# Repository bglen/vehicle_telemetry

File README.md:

# Vehicle Telemetry System

*Note: This is a work in progress and many features are not implemented yet.*

The Vehicle Telemetry System is an offline-first, containerized CAN data logging system. The system is designed to provide live telemetry and data logging for race cars, but can easilly be adapted to any mobile vehicle or robotic platform that uses CAN networks.

# Architecture Overview

### Current Features
- Logs CAN and decodes to CSV file
- Ability to decode using multiple DBC files
- Access and download decoded log files on the logger's local WiFi hotspot
- Handles sudden power loss gracefully
- Supports two CAN 2.0B networks up to 1 Mbps
- Logs data from NMEA format USB GPS devices

### Future Functionality
- Stores data to local influxDB database when logging offline. Syncs data to cloud database when internet access is detected.
- Bluetooth control of action cameras (GoPro, DJI Action)

# Data Logger

## Hardware Overview

This repo contains the hardware design for an open-source Raspberry Pi-based CAN data logger.

- Raspberry Pi 4 Model B
- 12V nominal power
- Can log two CAN networks
- GPIO for remote button for log start/stop and logging status LEDs
- Real time clock for accurate data time-stamps when not connected to internet
- Temperature, pressure, and humidity SPI sensor
- Bus voltage logging

## Datalogger Software Setup

1. Create a fresh install of Raspberry Pi OS on your Pi 4B
2. Connect to your Pi via SSH or other methods. Ensure it has an internet connection.
3. Update apt and install git and jq: `sudo apt upgrade -y && sudo apt install -y git jq`
4. Clone the repo: `git clone https://github.com/bglen/vehicle_telemetry`
5. Go to the setup folder: `cd vehicle_telemetry/software/datalogger/setup`
6. Make **install.sh** executable: `chmod +x install.sh`
7. Run the installer: `./install.sh`
8. During the install, enter in your preferred access point network name and trusted network details.
9. Reboot the Pi: `sudo reboot`

# Data Visualiation Tool

A python data visualization tool is provided and uses **rerun.io** to visualize .CSV log files.

## License
MIT License

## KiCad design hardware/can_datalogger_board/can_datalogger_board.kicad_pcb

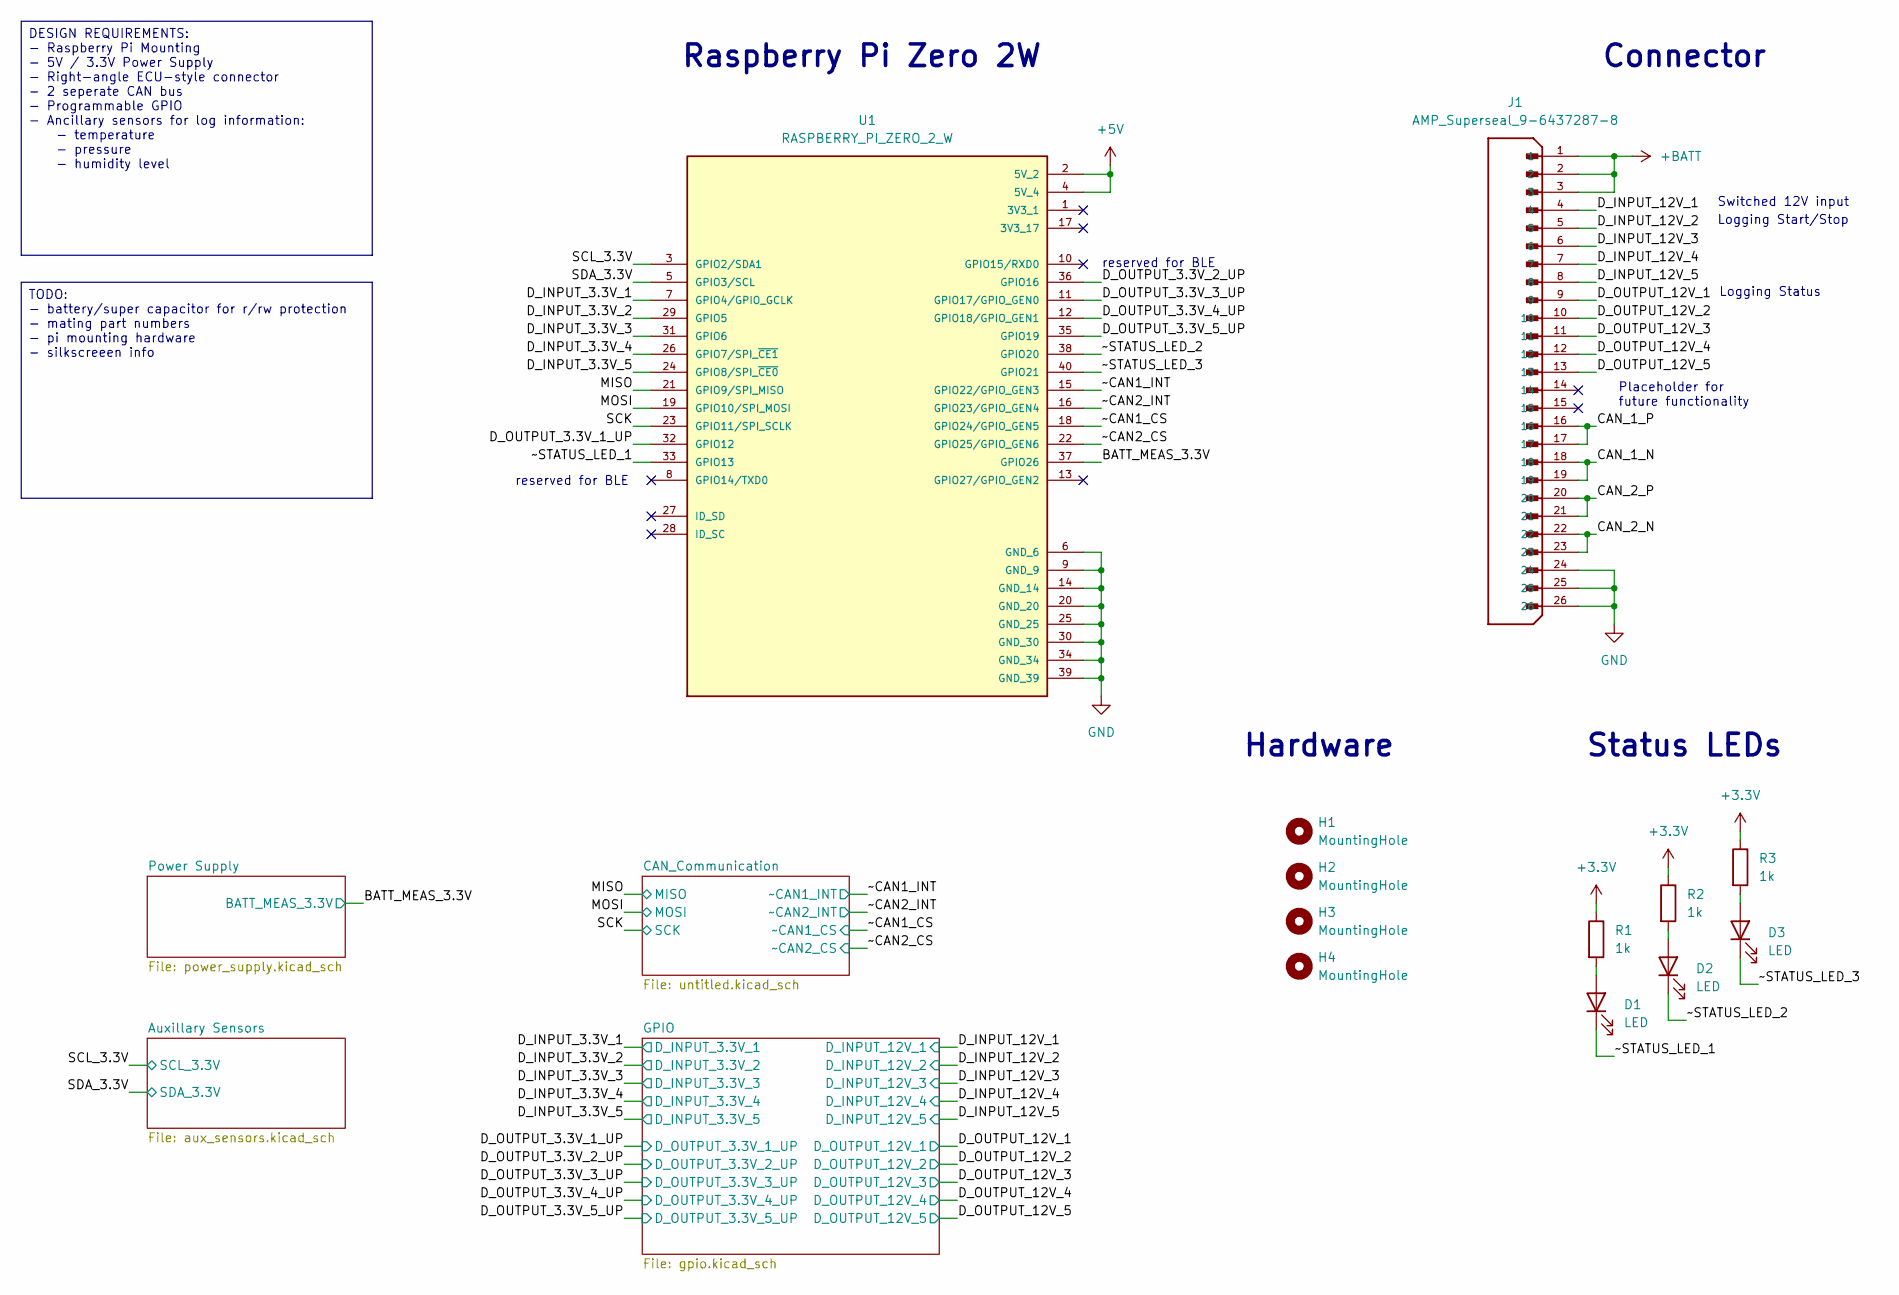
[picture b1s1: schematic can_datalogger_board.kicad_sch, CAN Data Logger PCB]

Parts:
D1, D2, D3: LED; LED_0603_1608Metric
H1, H2, H3, H4: MountingHole; MountingHole_3.2mm_M3
J1: AMP_Superseal_9-6437287-8; TE_9-6437287-8; PARTREV A1
R1, R2, R3: 1k; R_0603_1608Metric
U1: RASPBERRY_PI_ZERO_2_W; MODULE_RASPBERRY_PI_ZERO_2_W; PARTREV April 2024

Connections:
+3.3V: R1.1, R2.1, R3.1; also elsewhere on the board
+5V: U1.2 (5V_2), U1.4 (5V_4); also elsewhere on the board
+BATT: J1.1, J1.2, J1.3; also elsewhere on the board
/BATT_MEAS_3.3V: U1.37 (GPIO26)
/CAN_1_N: J1.18, J1.19
/CAN_1_P: J1.16, J1.17
/CAN_2_N: J1.22, J1.23
/CAN_2_P: J1.20, J1.21
/D_INPUT_3.3V_1: U1.7 (GPIO4/GPIO_GCLK); also elsewhere on the board
/D_INPUT_3.3V_2: U1.29 (GPIO5); also elsewhere on the board
/D_INPUT_3.3V_3: U1.31 (GPIO6); also elsewhere on the board
/D_INPUT_3.3V_4: U1.26 (GPIO7/SPI_~CE1); also elsewhere on the board
/D_INPUT_3.3V_5: U1.24 (GPIO8/SPI_~CE0); also elsewhere on the board
/D_INPUT_12V_1: J1.4; also elsewhere on the board
/D_INPUT_12V_2: J1.5; also elsewhere on the board
/D_INPUT_12V_3: J1.6; also elsewhere on the board
/D_INPUT_12V_4: J1.7; also elsewhere on the board
/D_INPUT_12V_5: J1.8; also elsewhere on the board
/D_OUTPUT_3.3V_1_UP: U1.32 (GPIO12); also elsewhere on the board
/D_OUTPUT_3.3V_2_UP: U1.36 (GPIO16); also elsewhere on the board
/D_OUTPUT_3.3V_3_UP: U1.11 (GPIO17/GPIO_GEN0); also elsewhere on the board
/D_OUTPUT_3.3V_4_UP: U1.12 (GPIO18/GPIO_GEN1); also elsewhere on the board
/D_OUTPUT_3.3V_5_UP: U1.35 (GPIO19); also elsewhere on the board
/D_OUTPUT_12V_1: J1.9; also elsewhere on the board
/D_OUTPUT_12V_2: J1.10; also elsewhere on the board
/D_OUTPUT_12V_3: J1.11; also elsewhere on the board
/D_OUTPUT_12V_4: J1.12; also elsewhere on the board
/D_OUTPUT_12V_5: J1.13; also elsewhere on the board
/MISO: U1.21 (GPIO9/SPI_MISO); also elsewhere on the board
/MOSI: U1.19 (GPIO10/SPI_MOSI); also elsewhere on the board
/SCK: U1.23 (GPIO11/SPI_SCLK); also elsewhere on the board
/SCL_3.3V: U1.3 (GPIO2/SDA1); also elsewhere on the board
/SDA_3.3V: U1.5 (GPIO3/SCL); also elsewhere on the board
/~CAN1_CS: U1.18 (GPIO24/GPIO_GEN5); also elsewhere on the board
/~CAN1_INT: U1.15 (GPIO22/GPIO_GEN3); also elsewhere on the board
/~CAN2_CS: U1.22 (GPIO25/GPIO_GEN6); also elsewhere on the board
/~CAN2_INT: U1.16 (GPIO23/GPIO_GEN4); also elsewhere on the board
/~STATUS_LED_1: D1.1 (K), U1.33 (GPIO13)
/~STATUS_LED_2: D2.1 (K), U1.38 (GPIO20)
/~STATUS_LED_3: D3.1 (K), U1.40 (GPIO21)
GND: J1.24, J1.25, J1.26, U1.6 (GND_6), U1.9 (GND_9), U1.14 (GND_14), U1.20 (GND_20), U1.25 (GND_25), U1.30 (GND_30), U1.34 (GND_34), U1.39 (GND_39); also elsewhere on the board
unnamed: D1.2 (A), R1.2
unnamed: D2.2 (A), R2.2
unnamed: D3.2 (A), R3.2

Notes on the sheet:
Switched 12V input
reserved for BLE
Status LEDs
Logging Start/Stop
Logging Status
Connector
Hardware
Raspberry Pi Zero 2W
Placeholder for future functionality
TODO: - battery/super capacitor for r/rw protection - mating part numbers - pi mounting hardware - silkscreeen info
DESIGN REQUIREMENTS: - Raspberry Pi Mounting - 5V / 3.3V Power Supply - Right-angle ECU-style connector - 2 seperate CAN bus - Programmable GPIO - Ancillary sensors for log information: - temperature - pressure - humidity level

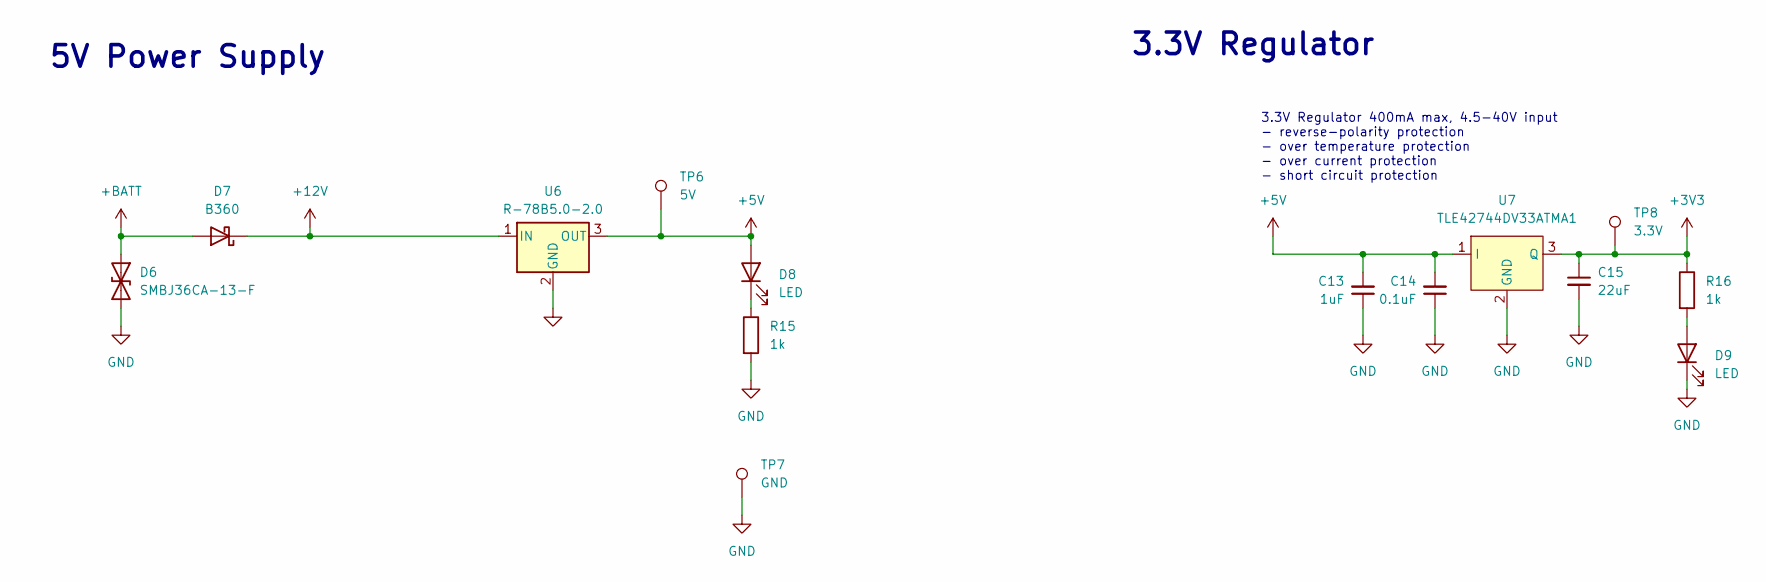
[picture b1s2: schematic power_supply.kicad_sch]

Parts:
C13: 1uF; C_0603_1608Metric
C14: 0.1uF; C_0603_1608Metric
C15: 22uF; C_0805_2012Metric
D6: SMBJ36CA-13-F; D_SMB
D7: B360; D_SMC
D8, D9: LED; LED_0603_1608Metric
R15, R16: 1k; R_0603_1608Metric
TP6: 5V; TestPoint_Pad_D1.0mm
TP7: GND; TestPoint_Pad_D1.0mm
TP8: 3.3V; TestPoint_Pad_D1.0mm
U6: R-78B5.0-2.0; Converter_DCDC_RECOM_R-78B-2.0_THT
U7: TLE42744DV33ATMA1; TO-252-3_TabPin2

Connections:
+3V3: C15.1, R16.1, TP8.1, U7.3 (Q); also elsewhere on the board
+5V: C13.2, C14.2, D8.2 (A), TP6.1, U6.3 (OUT), U7.1 (I); also elsewhere on the board
+12V: D7.1 (K), U6.1 (IN); also elsewhere on the board
+BATT: D6.1 (A1), D7.2 (A); also elsewhere on the board
GND: C13.1, C14.1, C15.2, D6.2 (A2), D9.1 (K), R15.2, TP7.1, U6.2 (GND), U7.2 (GND); also elsewhere on the board
unnamed: D8.1 (K), R15.1
unnamed: D9.2 (A), R16.2

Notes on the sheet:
3.3V Regulator
3.3V Regulator 400mA max, 4.5-40V input - reverse-polarity protection - over temperature protection - over current protection - short circuit protection
5V Power Supply

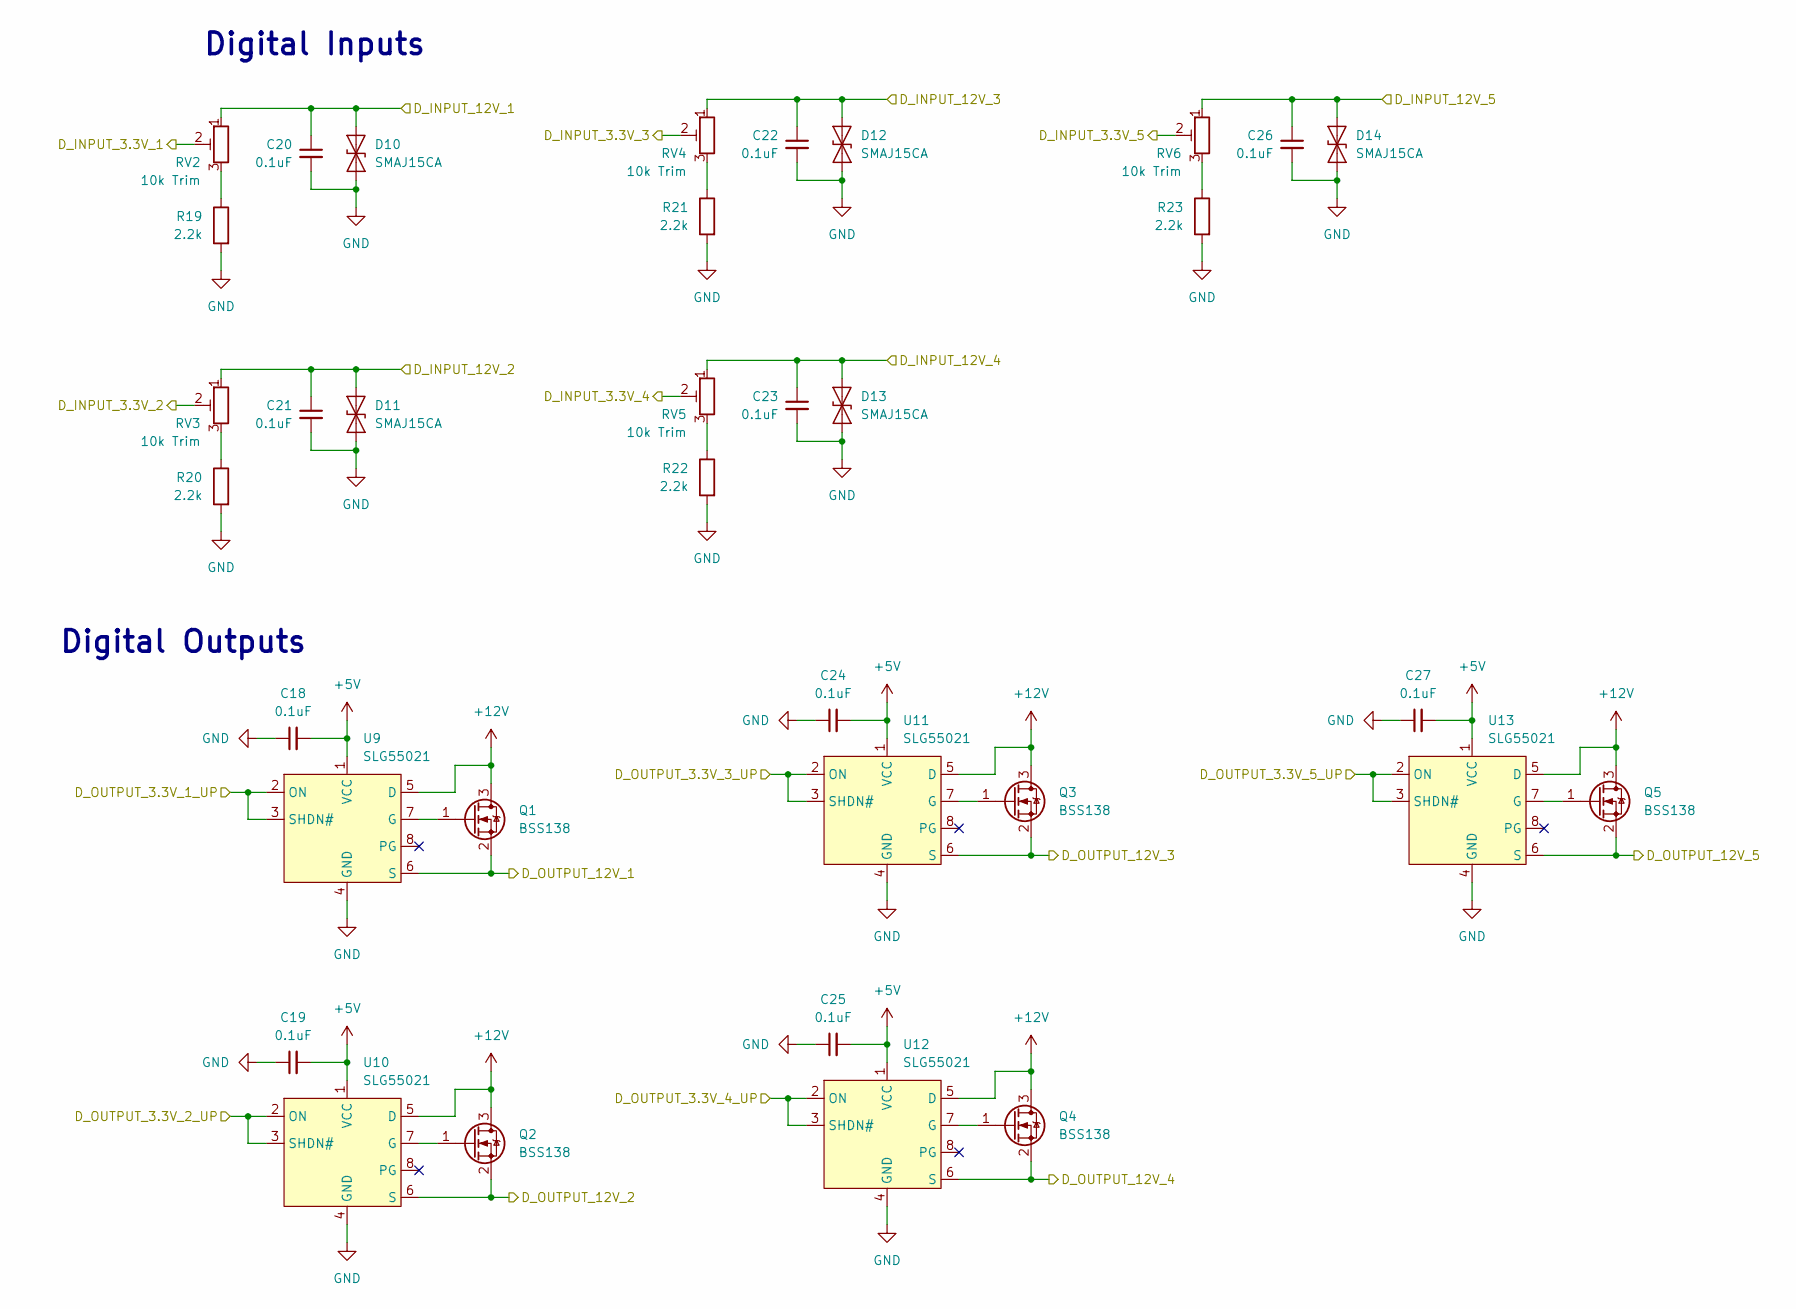
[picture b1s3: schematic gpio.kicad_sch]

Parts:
C18, C19, C20, C21, C22, C23, C24, C25, C26, C27: 0.1uF; C_0603_1608Metric
D10, D11, D12, D13, D14: SMAJ15CA; D_SMA
Q1, Q2, Q3, Q4, Q5: BSS138; SOT-23
R19, R20, R21, R22, R23: 2.2k; R_0603_1608Metric
RV2, RV3, RV4, RV5, RV6: 10k Trim; Potentiometer_Bourns_TC33X_Vertical
U9, U10, U11, U12, U13: SLG55021; TDFN-8-1EP_2x2mm_P0.5mm_EP0.8x1.2mm

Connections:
+5V: C18.2, C19.2, C24.2, C25.2, C27.2, U9.1 (VCC), U10.1 (VCC), U11.1 (VCC), U12.1 (VCC), U13.1 (VCC); also elsewhere on the board
+12V: Q1.3 (D), Q2.3 (D), Q3.3 (D), Q4.3 (D), Q5.3 (D), U9.5 (D), U10.5 (D), U11.5 (D), U12.5 (D), U13.5 (D); also elsewhere on the board
/D_INPUT_3.3V_1: RV2.2; also elsewhere on the board
/D_INPUT_3.3V_2: RV3.2; also elsewhere on the board
/D_INPUT_3.3V_3: RV4.2; also elsewhere on the board
/D_INPUT_3.3V_4: RV5.2; also elsewhere on the board
/D_INPUT_3.3V_5: RV6.2; also elsewhere on the board
/D_INPUT_12V_1: C20.1, D10.1 (A1), RV2.1; also elsewhere on the board
/D_INPUT_12V_2: C21.1, D11.1 (A1), RV3.1; also elsewhere on the board
/D_INPUT_12V_3: C22.1, D12.1 (A1), RV4.1; also elsewhere on the board
/D_INPUT_12V_4: C23.1, D13.1 (A1), RV5.1; also elsewhere on the board
/D_INPUT_12V_5: C26.1, D14.1 (A1), RV6.1; also elsewhere on the board
/D_OUTPUT_3.3V_1_UP: U9.2 (ON), U9.3 (SHDN#); also elsewhere on the board
/D_OUTPUT_3.3V_2_UP: U10.2 (ON), U10.3 (SHDN#); also elsewhere on the board
/D_OUTPUT_3.3V_3_UP: U11.2 (ON), U11.3 (SHDN#); also elsewhere on the board
/D_OUTPUT_3.3V_4_UP: U12.2 (ON), U12.3 (SHDN#); also elsewhere on the board
/D_OUTPUT_3.3V_5_UP: U13.2 (ON), U13.3 (SHDN#); also elsewhere on the board
/D_OUTPUT_12V_1: Q1.2 (S), U9.6 (S); also elsewhere on the board
/D_OUTPUT_12V_2: Q2.2 (S), U10.6 (S); also elsewhere on the board
/D_OUTPUT_12V_3: Q3.2 (S), U11.6 (S); also elsewhere on the board
/D_OUTPUT_12V_4: Q4.2 (S), U12.6 (S); also elsewhere on the board
/D_OUTPUT_12V_5: Q5.2 (S), U13.6 (S); also elsewhere on the board
GND: C18.1, C19.1, C20.2, C21.2, C22.2, C23.2, C24.1, C25.1, C26.2, C27.1, D10.2 (A2), D11.2 (A2), D12.2 (A2), D13.2 (A2), D14.2 (A2), R19.2, R20.2, R21.2, R22.2, R23.2, U9.4 (GND), U10.4 (GND), U11.4 (GND), U12.4 (GND), U13.4 (GND); also elsewhere on the board
unnamed: Q1.1 (G), U9.7 (G)
unnamed: Q2.1 (G), U10.7 (G)
unnamed: Q3.1 (G), U11.7 (G)
unnamed: Q4.1 (G), U12.7 (G)
unnamed: Q5.1 (G), U13.7 (G)
unnamed: R19.1, RV2.3
unnamed: R20.1, RV3.3
unnamed: R21.1, RV4.3
unnamed: R22.1, RV5.3
unnamed: R23.1, RV6.3

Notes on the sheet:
Digital Outputs
Digital Inputs

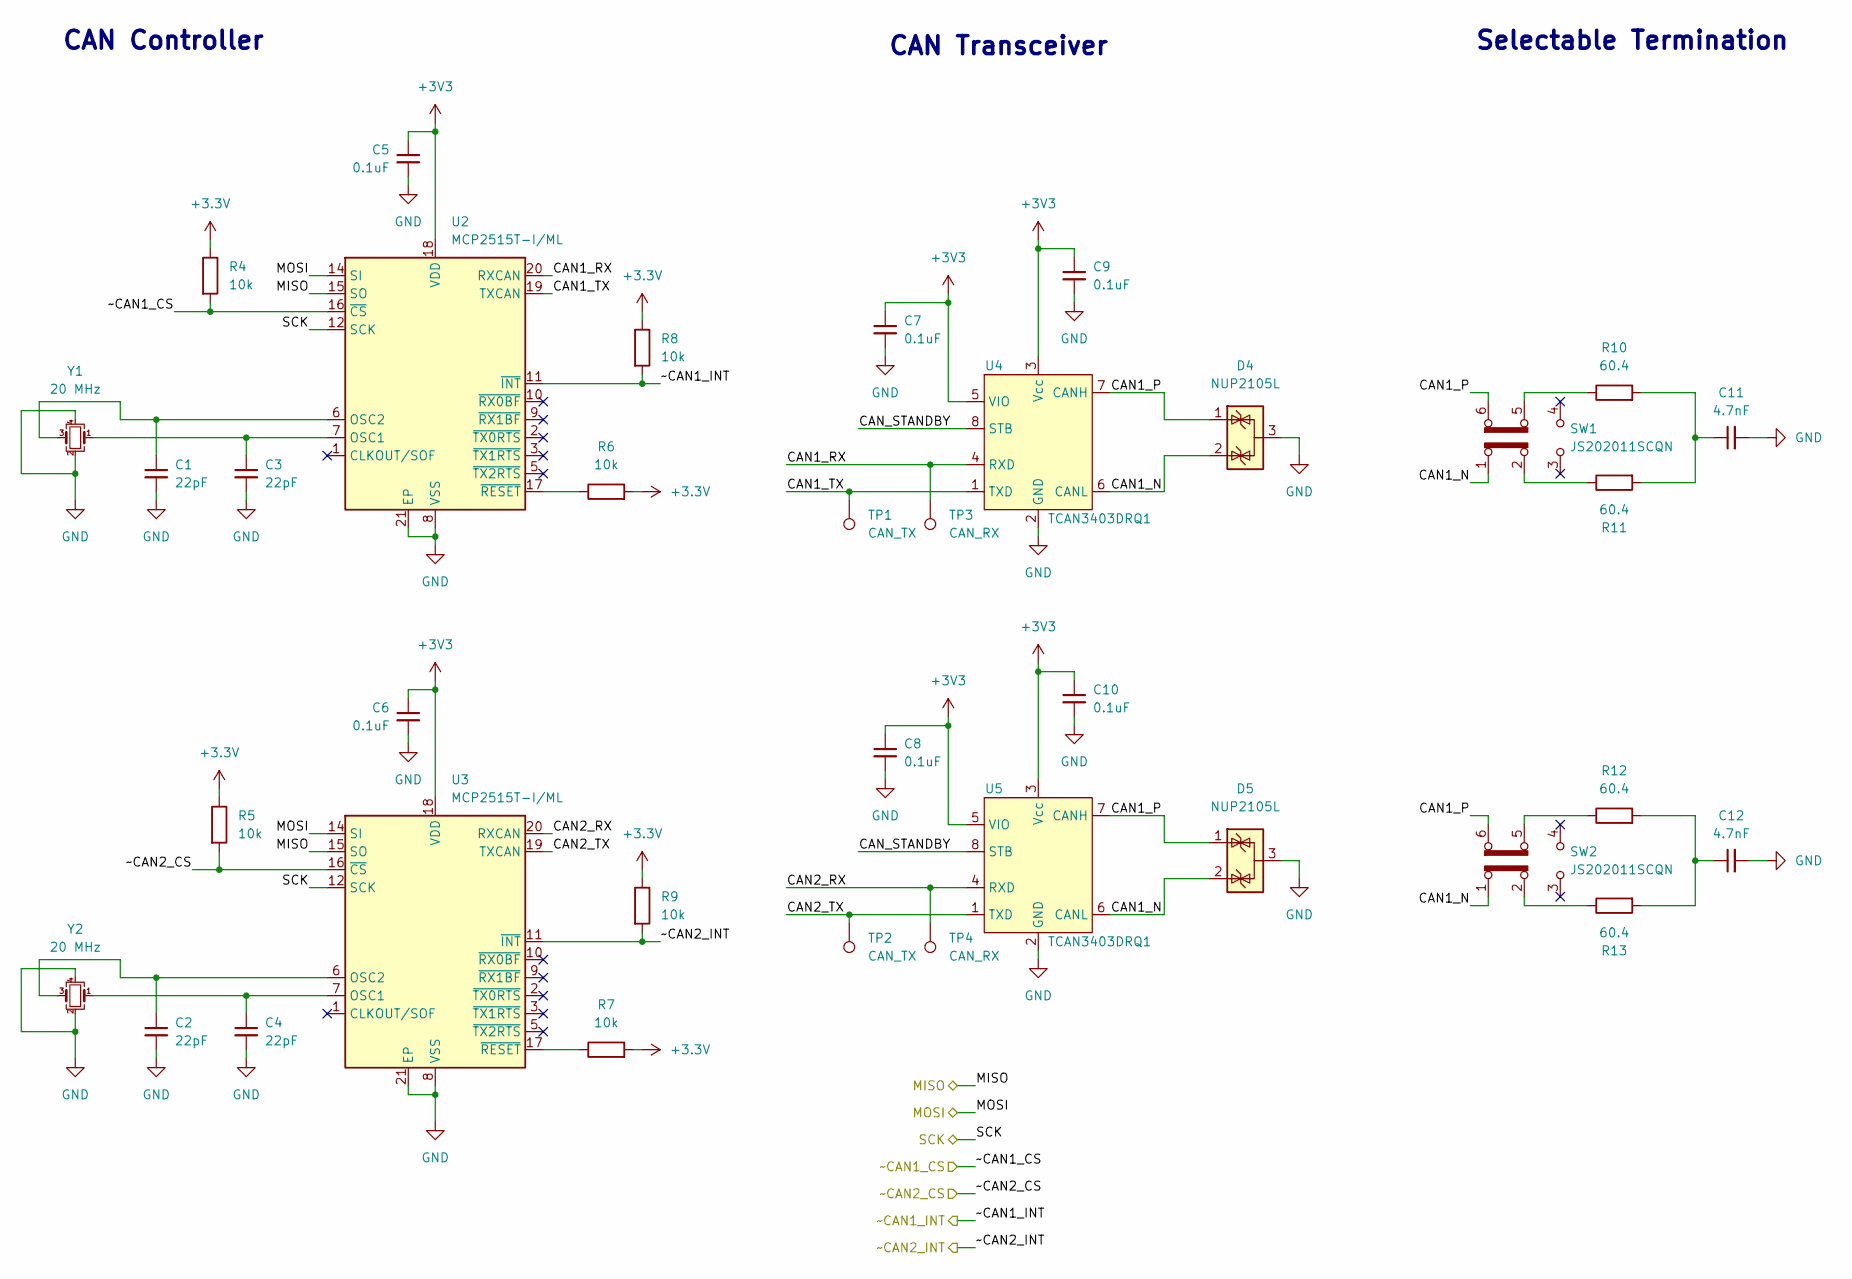
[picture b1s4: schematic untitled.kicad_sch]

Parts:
C1, C2, C3, C4: 22pF; C_0603_1608Metric
C5, C6, C7, C8, C9, C10: 0.1uF; C_0603_1608Metric
C11, C12: 4.7nF; C_0603_1608Metric
D4, D5: NUP2105L; SOT-23
R4, R5, R6, R7, R8, R9: 10k; R_0603_1608Metric
R10, R11, R12, R13: 60.4; R_0603_1608Metric
SW1, SW2: JS202011SCQN; SW_JS202011SCQN
TP1, TP2: CAN_TX; TestPoint_Pad_D1.0mm
TP3, TP4: CAN_RX; TestPoint_Pad_D1.0mm
U2, U3: MCP2515T-I/ML; QFN-20-1EP_4x4mm_P0.5mm_EP2.5x2.5mm
U4, U5: TCAN3403DRQ1; SOIC-8_3.9x4.9mm_P1.27mm
Y1, Y2: 20 MHz; Crystal_SMD_2520-4Pin_2.5x2.0mm

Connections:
+3.3V: R4.1, R5.1, R6.2, R7.2, R8.1, R9.1; also elsewhere on the board
+3V3: C5.1, C6.1, C7.1, C8.1, C9.1, C10.1, U2.18 (VDD), U3.18 (VDD), U4.3 (Vcc), U4.5 (VIO), U5.3 (Vcc), U5.5 (VIO); also elsewhere on the board
/CAN_Communication/CAN1_N: D4.2 (K), D5.2 (K), SW1.1 (A), SW2.1 (A), U4.6 (CANL), U5.6 (CANL)
/CAN_Communication/CAN1_P: D4.1 (K), D5.1 (K), SW1.6 (C), SW2.6 (C), U4.7 (CANH), U5.7 (CANH)
/CAN_Communication/CAN1_RX: TP3.1, U2.20 (RXCAN), U4.4 (RXD)
/CAN_Communication/CAN1_TX: TP1.1, U2.19 (TXCAN), U4.1 (TXD)
/CAN_Communication/CAN2_RX: TP4.1, U3.20 (RXCAN), U5.4 (RXD)
/CAN_Communication/CAN2_TX: TP2.1, U3.19 (TXCAN), U5.1 (TXD)
/CAN_Communication/CAN_STANDBY: U4.8 (STB), U5.8 (STB)
/MISO: U2.15 (SO), U3.15 (SO); also elsewhere on the board
/MOSI: U2.14 (SI), U3.14 (SI); also elsewhere on the board
/SCK: U2.12 (SCK), U3.12 (SCK); also elsewhere on the board
/~CAN1_CS: R4.2, U2.16 (~CS); also elsewhere on the board
/~CAN1_INT: R8.2, U2.11 (~INT); also elsewhere on the board
/~CAN2_CS: R5.2, U3.16 (~CS); also elsewhere on the board
/~CAN2_INT: R9.2, U3.11 (~INT); also elsewhere on the board
GND: C1.2, C2.2, C3.2, C4.2, C5.2, C6.2, C7.2, C8.2, C9.2, C10.2, C11.2, C12.2, D4.3 (A), D5.3 (A), U2.8 (VSS), U2.21 (EP), U3.8 (VSS), U3.21 (EP), U4.2 (GND), U5.2 (GND), Y1.2, Y1.4, Y2.2, Y2.4; also elsewhere on the board
unnamed: C11.1, R10.2, R11.2
unnamed: C12.1, R12.2, R13.2
unnamed: R10.1, SW1.5 (B)
unnamed: R11.1, SW1.2 (B)
unnamed: R12.1, SW2.5 (B)
unnamed: R13.1, SW2.2 (B)
unnamed: C3.1, U2.7 (OSC1), Y1.1
unnamed: C1.1, U2.6 (OSC2), Y1.3
unnamed: R6.1, U2.17 (~RESET)
unnamed: C4.1, U3.7 (OSC1), Y2.1
unnamed: C2.1, U3.6 (OSC2), Y2.3
unnamed: R7.1, U3.17 (~RESET)

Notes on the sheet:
Selectable Termination
CAN Transceiver
CAN Controller

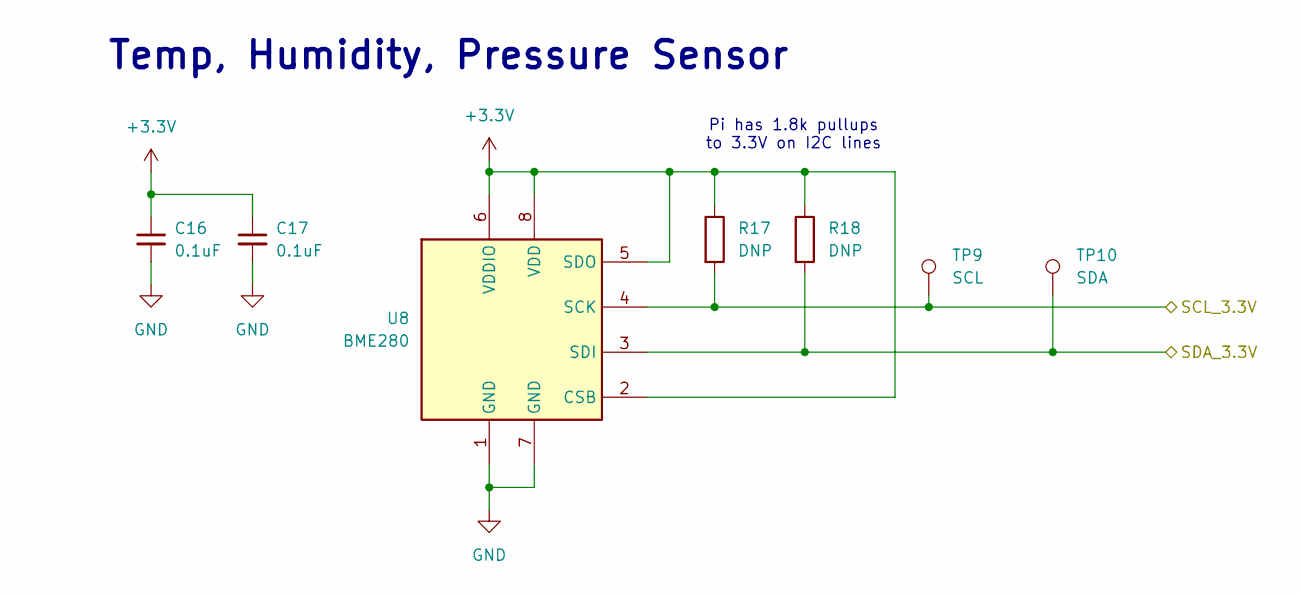
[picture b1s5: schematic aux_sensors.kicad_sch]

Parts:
C16, C17: 0.1uF; C_0603_1608Metric
R17, R18: DNP; R_0603_1608Metric
TP9: SCL; TestPoint_Pad_D1.0mm
TP10: SDA; TestPoint_Pad_D1.0mm
U8: BME280; Bosch_LGA-8_2.5x2.5mm_P0.65mm_ClockwisePinNumbering

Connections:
+3.3V: C16.1, C17.1, R17.1, R18.1, U8.2 (CSB), U8.5 (SDO), U8.6 (VDDIO), U8.8 (VDD); also elsewhere on the board
/SCL_3.3V: R17.2, TP9.1, U8.4 (SCK); also elsewhere on the board
/SDA_3.3V: R18.2, TP10.1, U8.3 (SDI); also elsewhere on the board
GND: C16.2, C17.2, U8.1 (GND), U8.7 (GND); also elsewhere on the board

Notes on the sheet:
Pi has 1.8k pullups to 3.3V on I2C lines
Temp, Humidity, Pressure Sensor

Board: 2 copper layers, 104 parts (1 on the bottom side), 76 nets, no tracks yet.

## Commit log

2025-03-28 Also log raw messaged which cannot be decoded by DBC
2025-03-28 CAD data for logger enclosure
2025-03-28 Enable CAN0 from script instead of service
    Also updated naming conventions
2025-03-28 Updated README
    Installing dependencies
2025-03-29 Updated button to reduce wiring
    Also organized gpio setup
2025-03-29 Updated paths to be user generic
2025-03-29 fixing event detection upon multiple script calls
2025-03-29 Switched to using gpiozero library
2025-03-29 fixed debouncing
2025-03-29 fixed bug with can interface already brought up before script starts
2025-03-29 bring down can interface upon keyboard interrupt
2025-03-29 Improve button de-bounce
2025-03-29 removed depreceated argument bustype
2025-03-29 Added clear logs function
2025-03-29 fixed blocking issue
2025-03-29 Updated auto-start to use virtual environment
2025-03-29 Fixed auto start and updated README
2025-05-27 PCB schematic rev 1.0
2025-05-28 Fixed LED turning on at boot
2025-05-29 Updated gitignore, README.md
2025-05-29 Updated service to be simpler
2025-05-29 Flask webapp for downloading logs
2025-05-29 updated page style and table format
2025-05-30 Plotly dash app for data analysis
2025-06-01 Updated CSV naming format
2025-06-01 Updated CSV output format
    Each column is a separate signal. Multiple devices supported, as column naming is "message_name_signal"
2025-06-11 PCB component placement
2025-06-11 added rename function
2025-07-18 minor updates
2025-07-18 Added architecture documentation
2025-07-19 re-org
    - added docker image of influxDB
2025-07-19 env file
2025-07-19 Updated video architecture
2025-07-24 Logging support for VK-162 USB GPS
2025-07-24 Separated can functionality from main script
2025-08-08 Refactor datalogging pi service
    1. repo directory structure refactor
    2. creation of a install.sh script for the pi
    3. Improved WiFi service: use trusted networks, or if none exist, start an access point. Makes debugging and testing of new software at home much easier since it connects to a trusted network with in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
2025-08-08 Fixed directory and hostapd masking issue
    Also updated readme
2025-08-08 Added setup info regarding network settings
    - Also a check to ensure the venv is activated during the install.sh
2025-08-08 Fix wifi_manager.py to use NetworkManager
    Also brings up static ip when in AP mode
2025-08-08 reboot option in install.sh
2025-08-09 Use NetworkManager for access point
    Also: wifi configuration directly in the setup script
2025-08-15 HTTP file server service
    exposes the software/datalogger/logs/ directory on datalogger.local
2025-08-15 Start of telemetry visualizer using rerun.io
2025-08-15 Simplified install
    - 1 less command
    - less ambiguity on AP SSID
    - file server at datalogger.local not datalogger.local:8000
2025-08-15 Support for multiple-DBC live decoding
2025-08-16 added packeges to requirements.txt
2025-08-16 more dependencies
2025-08-16 more req cleaning whoops
2025-08-18 minor fixes
